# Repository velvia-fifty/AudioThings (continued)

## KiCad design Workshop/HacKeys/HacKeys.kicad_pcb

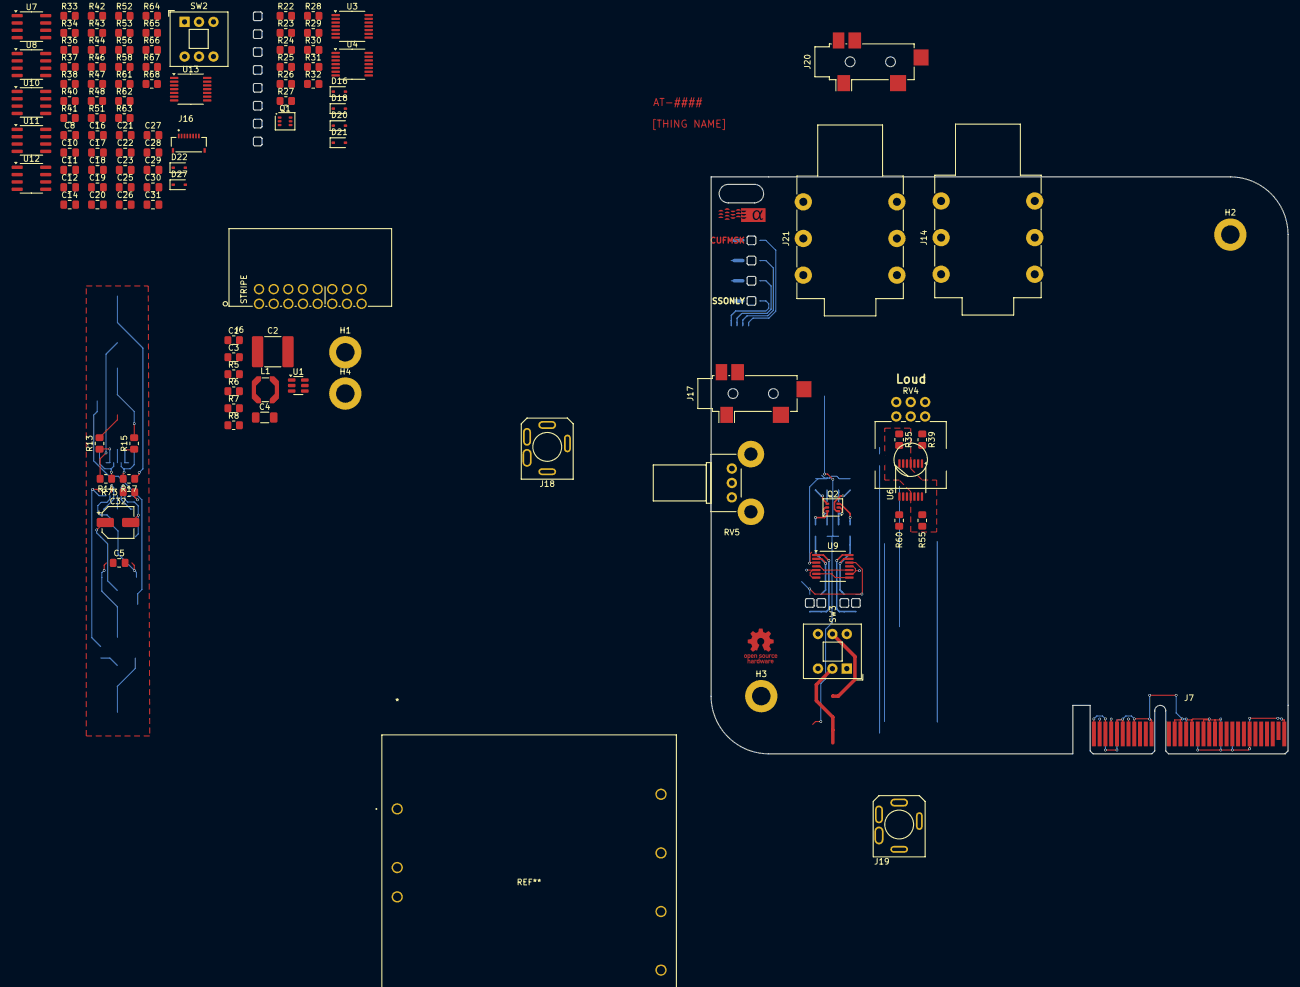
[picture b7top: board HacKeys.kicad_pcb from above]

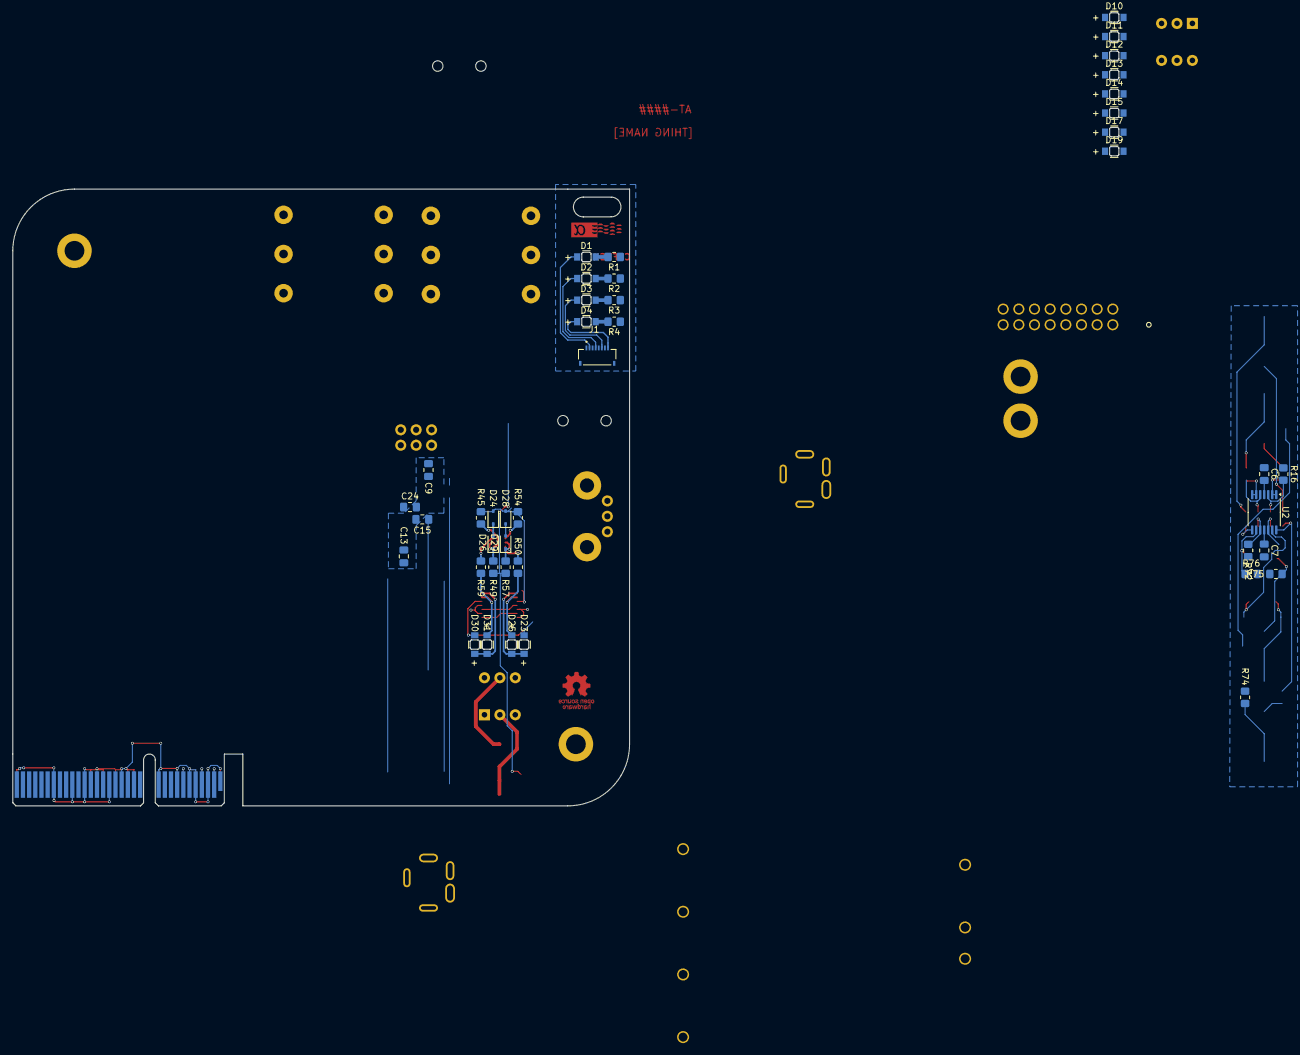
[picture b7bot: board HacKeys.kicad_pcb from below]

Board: 2 copper layers, 158 parts (27 on the bottom side), 111 nets.

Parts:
C1: 100nF; R_0805_2012Metric_Pad1.20x1.40mm_HandSolder
C2: 4.7uF; C_2220_5750Metric_Pad1.97x5.40mm_HandSolder
C3: 0.1uF; R_0805_2012Metric_Pad1.20x1.40mm_HandSolder
C4: 15uF; C_1206_3216Metric_Pad1.33x1.80mm_HandSolder
C5, C8, C9, C11, C13: 100pF; C_0805_2012Metric_Pad1.18x1.45mm_HandSolder
C6, C7, C14, C15, C16, C17, C18, C19, C20, C21, C22, C23, C24, C25, C26, C27, C28, C29, C30, C31: 100nF; C_0805_2012Metric_Pad1.18x1.45mm_HandSolder
C10, C12: 47uf / 16v; C_0805_2012Metric_Pad1.18x1.45mm_HandSolder
C32: 10uF; CP_Elec_5x5.4
D1, D10, D11: LED (Red); WL-SMRD_1205
D2, D12, D13: LED (Yellow); WL-SMRD_1205
D3, D14, D15, D17, D19: LED (Green); WL-SMRD_1205
D4: LED (Blue); WL-SMRD_1205
D16, D18, D20, D21, D22, D24, D26, D27, D28, D29: 1N4148WS; D_SOD-323
D23, D30: Red +6dB; WL-SMRD_1205
D25, D31: Yellow +3dB; WL-SMRD_1205
GFX1: FRONT PANEL AT LOGO; at-logo-cu
GFX2: FRONT PANEL OSHW; OSHW-Logo_5.7x6mm_Copper
H1, H2, H3, H4: M3; MountingHole_3.2mm_M3_DIN965_Pad
J1: FRONT PANEL MAGIC; AMPHENOL_F33B-1A7Q1-E8C08
J6: OPT EURO; EURORACK Right Angle
J7: BUS_PCIexpress_x4
J14: FX SEND; Quarter Inch
J16: EXT Outs; AMPHENOL_F33B-1A7Q1-E8C08
J17: TO FX; Jack_3.5mm_CUI_SJ2-3593D-SMT_Horizontal
J18: Out; SJ3-3505
J19: IN; SJ3-3505
J20: FROM FX; Jack_3.5mm_CUI_SJ2-3593D-SMT_Horizontal
J21: FX RETURN; Quarter Inch
L1: 12uH; L_Coilcraft_LPS4414
Q1, Q2: BC857BDW1Ts; SOT-363_SC-70-6
R1, R2, R3: 150R; R_0805_2012Metric_Pad1.20x1.40mm_HandSolder
R4, R43, R44, R46, R64, R65, R66: 100R; R_0805_2012Metric_Pad1.20x1.40mm_HandSolder
R5: 1.37M; R_0805_2012Metric_Pad1.20x1.40mm_HandSolder
R6: 255k; R_0805_2012Metric_Pad1.20x1.40mm_HandSolder
R7: 178k; R_0805_2012Metric_Pad1.20x1.40mm_HandSolder
R8: 22.1k; R_0805_2012Metric_Pad1.20x1.40mm_HandSolder
R13, R15, R16, R24, R35, R38, R40, R55, R58, R61, R74: 1k; R_0805_2012Metric_Pad1.20x1.40mm_HandSolder
R14, R37, R52: 20k; R_0805_2012Metric_Pad1.20x1.40mm_HandSolder
R17, R22, R39, R60: 2k; R_0805_2012Metric_Pad1.20x1.40mm_HandSolder
R23, R25: 820R; R_0805_2012Metric_Pad1.20x1.40mm_HandSolder
R26: 200R; R_0805_2012Metric_Pad1.20x1.40mm_HandSolder
R27, R28, R45, R54: 180R; R_0805_2012Metric_Pad1.20x1.40mm_HandSolder
R29, R30, R49, R57: 22k; R_0805_2012Metric_Pad1.20x1.40mm_HandSolder
R31, R32, R50, R59: 3k3; R_0805_2012Metric_Pad1.20x1.40mm_HandSolder
R33, R36, R41, R42, R53, R56, R62, R63: 10R; R_0805_2012Metric_Pad1.20x1.40mm_HandSolder
R34, R51: 16k; R_0805_2012Metric_Pad1.20x1.40mm_HandSolder
R47, R48, R67, R68, R73: 10k; R_0805_2012Metric_Pad1.20x1.40mm_HandSolder
R72: 470R; R_0805_2012Metric_Pad1.20x1.40mm_HandSolder
R75: 1M; R_0805_2012Metric_Pad1.20x1.40mm_HandSolder
R76: 150k; R_0805_2012Metric_Pad1.20x1.40mm_HandSolder
RV4: 10k; 2hp_Alps_RK09L_Double_Vertical
RV5: 10k; Potentiometer_Bourns_PTV09A-2_Single_Horizontal
SW2: -3dB Cut; SW_Push_2P2T_Toggle_CK_PVA2xxH4xxxxxxV2
SW3: Phones/Line; SW_Push_2P2T_Toggle_CK_PVA2xxH4xxxxxxV2
U1: TPS560430XDBVR; SOT-23-6
U2, U6, U13: TL074; TSSOP-14_4.4x5mm_P0.65mm
U3, U4, U9: LM339; TSSOP-14_4.4x5mm_P0.65mm
U7, U8, U10, U11, U12: NE5532; SOIC-8_3.9x4.9mm_P1.27mm

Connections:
9V: C4.1, L1.2, R7.1
+5V: J6.11, J6.12, J7.A2 (+5V), J7.B2 (+5V)
+12v: C2.1, C3.1, C6.2, C14.2, C15.2, C16.2, C17.2, C18.2, C19.2, C20.2, C21.2, C22.2, D16.2 (A), D18.2 (A), D24.2 (A), D28.2 (A), J6.9, J6.10, J7.A4 (+12V), J7.B4 (+12V), R5.1, R22.2, R27.2, R28.2, R45.2, R54.2, U1.5 (VIN), U2.4 (V+), U6.11 (V-), U7.8 (V+), U8.8 (V+), U9.3 (V+), U10.8 (V+), U11.8 (V+), U12.8 (V+), U13.11 (V-)
-12V: J6.1, J6.2, J7.A7 (-12V), J7.B7 (-12V)
-12v: C7.1, C23.1, C24.1, C25.1, C26.1, C27.1, C28.1, C29.1, C30.1, C31.1, D10.1 (K), D11.1 (K), D23.1 (K), D30.1 (K), U2.11 (V-), U6.4 (V+), U7.4 (V-), U8.4 (V-), U9.12 (V-), U10.4 (V-), U11.4 (V-), U12.4 (V-), U13.4 (V+)
/Bus/CON_CV: J6.13, J6.14, J7.A10 (EURO_CV)
/Bus/CON_GATE: J6.15, J6.16, J7.A9 (EURO_GATE)
/Headphone/+3 dB REF: U9.4 (-), U9.10 (-)
/Headphone/+6 dB REF: U9.6 (-), U9.8 (-)
/Headphone/OUT BAL L N: J16.5, R46.1
/Headphone/OUT BAL L P: J16.4, R44.1, SW3.6 (C)
/Headphone/OUT BAL R N: J16.8, R66.1
/Headphone/OUT BAL R P: J16.7, R65.1, SW3.3 (C)
/Headphone/OUT HP L: J16.1, R33.1, R36.1, R41.1, R42.1, SW3.4 (A)
/Headphone/OUT HP R: J16.2, R53.1, R56.1, R62.1, R63.1, SW3.1 (A)
/VU/0 dB REF: R24.1, R25.2, U3.6 (-), U4.6 (-)
/VU/+3 dB REF: R23.1, R24.2, U3.10 (-), U4.10 (-)
/VU/+6 dB REF: R22.1, R23.2, U3.8 (-), U4.8 (-)
/VU/-18 dB REF: R25.1, R26.2, U3.4 (-), U4.4 (-)
FX RETURN L: J20.T, R74.2, RV5.3
FX SEND A: J17.T, R14.1
GND: C2.2, C3.2, C4.2, C6.1, C7.2, C14.1, C15.1, C16.1, C17.1, C18.1, C19.1, C20.1, C21.1, C22.1, C23.2, C24.2, C25.2, C26.2, C27.2, C28.2, C29.2, C30.2, C31.2, J1.1, J1.3, J1.5, J1.7, J1.SH1, J1.SH2, J6.3, J6.4, J6.5, J6.6, J6.7, J6.8, J7.A3 (GND), J7.A5 (GND), J7.A6 (GND), J7.A8 (GND), J7.A11 (GND), J7.A15 (GND), J7.A17 (GND), J7.A19 (GND), J7.A21 (GND), J7.A23 (GND), J7.A26 (GND), J7.B1 (GND), J7.B3 (GND), J7.B5 (GND), J7.B6 (GND), J7.B8 (GND), J7.B11 (GND), J7.B13 (GND), J7.B14 (GND), J7.B16 (GND), J7.B18 (GND), J7.B20 (GND), J7.B26 (GND), J7.B32 (GND), J14.S, J16.3, J16.6, J16.SH1, J16.SH2, J17.S, J18.S, J20.S, J21.S, R1.1, R2.1, R3.1, R4.1, R6.2, R8.2, R16.1, R26.1, R29.1, R30.1, R49.1, R57.1, R72.1, R75.1, R76.1, U1.2 (GND), U2.12 (+), U6.5 (+), U6.12 (+), U7.3 (+), U8.5 (+), U11.3 (+), U12.5 (+)
LED BLU: D4.2 (A), J1.8
LED GRN: D3.2 (A), J1.6
LED RED: D1.2 (A), J1.2
LED YLW: D2.2 (A), J1.4
unnamed: C5.2, R15.1, RV5.1, U2.14
unnamed: C8.1, R34.2, R37.1
unnamed: C8.2, C10.1, R34.1
unnamed: C11.1, R51.2, R52.1
unnamed: C11.2, C12.1, R51.1
unnamed: C32.1, J21.T, R75.2
unnamed: D1.1 (K), R1.2
unnamed: D2.1 (K), R2.2
unnamed: D3.1 (K), R3.2
unnamed: D4.1 (K), R4.2
unnamed: D10.2 (A), D12.1 (K), U3.14
unnamed: D11.2 (A), D13.1 (K), U4.14
unnamed: D12.2 (A), D14.1 (K), U3.13
unnamed: D13.2 (A), D15.1 (K), U4.13
unnamed: D14.2 (A), D17.1 (K), U3.1
unnamed: D15.2 (A), D19.1 (K), U4.1
unnamed: D16.1 (K), D20.2 (A)
unnamed: D17.2 (A), R31.1, U3.2
unnamed: D18.1 (K), D21.2 (A)
unnamed: D19.2 (A), R32.1, U4.2
unnamed: D20.1 (K), Q1.5 (B2), R29.2
unnamed: D21.1 (K), Q1.2 (B1), R30.2
unnamed: D22.2 (A), SW2.3 (C)
unnamed: C10.2, D22.1 (K)
unnamed: D23.2 (A), D25.1 (K), U9.1
unnamed: D24.1 (K), D26.2 (A)
unnamed: D25.2 (A), R50.1, U9.2
unnamed: D26.1 (K), Q2.2 (B1), R49.2
unnamed: D27.2 (A), SW2.6 (C)
unnamed: C12.2, D27.1 (K)
unnamed: D28.1 (K), D29.2 (A)
unnamed: D29.1 (K), Q2.5 (B2), R57.2
unnamed: D30.2 (A), D31.1 (K), U9.14
unnamed: D31.2 (A), R59.1, U9.13
unnamed: J14.T, R13.2
unnamed: Q1.6 (C1), R32.2
unnamed: Q1.1 (E1), R28.1
unnamed: Q1.3 (C2), R31.2
unnamed: Q1.4 (E2), R27.1
unnamed: Q2.6 (C1), R50.2
unnamed: Q2.1 (E1), R45.1
unnamed: Q2.3 (C2), R59.2
unnamed: Q2.4 (E2), R54.1
unnamed: R46.2, R48.1, U8.7
unnamed: R66.2, R68.1, U12.7
unnamed: R73.2, R74.1, U2.8
unnamed: R37.2, SW2.1 (A)
unnamed: R52.2, SW2.4 (A)
unnamed: J18.R, SW3.2 (B)
unnamed: J18.T, SW3.5 (B)
unnamed: C1.1, U1.1 (CB)
unnamed: R5.2, R6.1, U1.4 (EN)
unnamed: R7.2, R8.1, U1.3 (FB)
unnamed: C1.2, L1.1, U1.6 (SW)
unnamed: R14.2, R16.2, U2.3 (+)
unnamed: R13.1, U2.1, U2.2 (-)
unnamed: RV5.2, U2.5 (+)
unnamed: R17.2, U2.6 (-), U2.7
unnamed: R72.2, R73.1, U2.10 (+)
unnamed: C32.2, R76.2, U2.9 (-)
unnamed: C5.1, R15.2, R17.1, U2.13 (-)
unnamed: U3.5 (+), U3.7 (+), U3.9 (+), U3.11 (+)
unnamed: U4.5 (+), U4.7 (+), U4.9 (+), U4.11 (+)
unnamed: R38.1, R41.2, U7.1, U7.5 (+)
unnamed: RV4.2, U6.3 (+)
unnamed: R39.2, U6.1, U6.2 (-)
unnamed: C9.1, R35.2, R39.1, U6.6 (-)
unnamed: RV4.5, U6.10 (+)
unnamed: R60.2, U6.8, U6.9 (-)
unnamed: C13.1, R55.2, R60.1, U6.13 (-)
unnamed: R38.2, R40.1, U7.2 (-)
unnamed: R42.2, U7.6 (-), U7.7
unnamed: R43.1, U8.3 (+)
unnamed: R44.2, U8.1, U8.2 (-)
unnamed: R47.1, R48.2, U8.6 (-)
unnamed: C9.2, R35.1, R40.2, R43.2, R47.2, RV4.1, U6.7, U9.5 (+), U9.7 (+)
unnamed: C13.2, R55.1, R61.2, R64.2, R67.2, RV4.4, U6.14, U9.9 (+), U9.11 (+)
unnamed: R58.1, R62.2, U10.3 (+), U10.5 (+), U11.1, U11.5 (+)
unnamed: R53.2, U10.1, U10.2 (-)
unnamed: R56.2, U10.6 (-), U10.7
unnamed: R58.2, R61.1, U11.2 (-)
unnamed: R63.2, U11.6 (-), U11.7
unnamed: R64.1, U12.3 (+)
unnamed: R65.2, U12.1, U12.2 (-)
unnamed: R67.1, R68.2, U12.6 (-)
